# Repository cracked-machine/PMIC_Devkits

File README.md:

# <U>STPMIC1 / PF3000 PMIC Dev Board</U>

#### Overview

Dual development board for evaluating two power management integrated circuits (PMIC) chips:

- STMicroElectronics STPMIC1
- NXP PF3000 Power Management ICs.

These are organised into two independantly powered sub-systems.

Each sub-system has a number of external power/signal connectors, along with a list of the jumpers used to configure how those connectors are routed to/from the PMIC chip. The PMICs are configured directly by modifying registers using either a MCU/MPU via the I2C connectors.

Each output has an LED indicator and testpoint. 
_Note_ that the LED will only light if the PMIC output voltage is set above 2V.

#### Circuit design notes
The schematic has a separate sheet for both sub-systems. There is one for each chip: 

- __DEV__ - The development board sub-system including power/config connectors.
- __MAIN__ - The individual PMIC including the required passive components for bypassing and SMPS/regulator operation. Designed to be reuseable blocks that can easily be incorproated into an existing design.

| STPMIC1 DEV | STPMIC1 MAIN |
|:---:|:---:|
||

| PF3000 DEV | PF3000 MAIN  |
|:---:|:---:|
|||

#### PCB layout notes
This is a four layer PCB design. The layer stackup is:

1. Signal
2. Ground
3. Small signal and power
4. Small signal and ground

Note the ground planes in layer 2 and 4 are connected.

The _docs_ directory contains:
- RevA gerber build files.
- [Bill of Materials](STPMIC1_MC32PF3000_Board/STPMIC1_MC32PF3000_Board/docs/bom/FULL_STPMIC1_MC32PF3000_Board.csv)
- CPL pick and place files.
- Related vendor application notes, datasheets and reference designs.

Custom symbols and footprints used in this project can be found in the [KicadLibrary](https://github.com/cracked-machine/KicadLibrary) repository.

## <U>PMIC #1: NXP PF300</U>

#### <U>Board connector definitions</U>

| Connector | Description | Comment |
|:---:|:---:|:---|
|J15|Wall adaptor power input|3.7V - 5.5V<br>DC Barrel 2.1mm|
|J12|Battery power input|3.1V - 4.5V<br>2.54mm Header|
|J20|I2C debug|1: Ground<br>2: SCL<br>3: SDA|
|J23|Digital Interface<br>(see datasheet)|1: Ground<br>2: STANDBY<br>3: RESETBMCU<br>4: SD_VSEL<br>5: INTB<br>6: PWRON|
|J21|PF3000 Power Output|Ground:<br>2,4,6,8,10,12,14,16,18,20,22,24,26<br><br>1: SW1B Buck <br>3: SW1A Buck <br>5: SWBST Boost<br>7: VSNVS LDO<br>9: VCCSD LDO<br>11: V33 LDO<br> 13: SW3 Buck<br>15: VREFDDR LDO<br>17: LDO4<br> 19: LDO3<br>21: SW2 Buck<br>23: LDO2<br> 25: LDO1

#### <U>Board jumper and switch definitions</U>

Warning: function of jumpers can be inverted using the registers. See datasheet for details.

| Jumper/Switch | Description| Setting | Comment |
|:---:|:---:|:---:|:---|
|JP1|Q2 Pullup|ON|Force Q2 gate to VDBG rail. <br>Use if PGOOD LED becomes erratic.|
|JP2|Q3 Pullup|ON|Force Q3 to VDBG rail. <br>Use if FAIL LED becomes erratic.|
|J13|OTP|3-2|Load OTP values from memory into OTP registers|
|J13|OTP|2-1|Disable OTP memory and load OTP values from fuses. "Try before buy" mode.|
|J16|I2C Bus Power (VDDIO)|3-2|Power from VDGB. 3.3V|
|J16|I2C Bus Power (VDDIO)|2-1|Power from Buck 2 output. 1.8V|
|J14|Digital Interface Power (V_PU)|3-2|Power from J16 output|
|J14|Digital Interface Power (V_PU)|2-1|Power from VSNVS output (fixed 3V)|
|J17|Standby|3-2|Enter standby mode|
|J17|Standby|2-1|Exit standby mode|
|J18|VCC_SD output range|3-2|1.8V to 1.85V|
|J18|VCC_SD output range|2-1|2.85V to 3.3V|
|J19|Power enable|2-1|IC power output is enabled|
|SW5|Power enable| - | Momentary SPST.<br>IC power output is enabled.
|J22|VPWR override|3-2|VPWR enable. <br>Set when J15 DC connector is powered|
|J22|VPWR override|2-1|VPWR disable. <br>Set when J12 battery power connector is powered.<br>Warning: Shorts J15 to ground!|

## <U>PMIC #2: STMicroelectronics STPMIC1</U>

#### <U>Board connector definitions</U>

| Connector | Description | Comment |
|:---:|:---:|:---|
|J2|External VIO|0.5V to 4.2V.<br>I/O voltage (for all digital signals except WAKEUP and PONKEY)|
|J3|External SWIN|0.5V - 7V.<br>External power source for VSWIN pin.
|J4|Wall adaptor power input|0.5V - 7V.<br>DC Barrel 2.1mm|
|J1|Battery power input|0.5V - 7V.<br>2.54mm Header|
|J10|I2C debug|1: Ground<br>2: SCL<br>3: SDA|
|J5|Digital Interface<br>(see datasheet)|1: Ground<br>2: PONKEY (IN)<br>3: WAKEUP (IN)<br>4: RST (BOTH)<br>5: PWRCTL (IN)<br>6: INT (OUT)|
|J21|STPMIC1 Power Output|Ground:<br>2,4,6,8,10,12,14,16,18,20,22,24,26<br><br>1: Buck2 <br>3: Buck1 <br>5: LDO4<br>7: VSWOUT LDO<br>9: VOTG LDO<br>11: Boost<br> 13: Buck3<br>15: Buck4<br>17: LDO1<br> 19: LDO6<br>21: LDO5<br>23: LDO2<br> 25: VREFDDR LDO<br>27: LDO3|

#### <U>Board jumper and switch definitions</U>

Warning: function of jumpers can be inverted using the registers. See datasheet for details.

| Jumper/Switch | Description| Setting | Comment |
|:---:|:---:|:---:|:---|
|J6|VIO source select|3-2|Power source from Buck3 output|
|J6|VIO source select|2-1|Power source from VIO Ext (J2)|
|J7|VSWIN source select|3-2|Power source from BOOST output|
|J7|VSWIN source select|2-1|Power source from SWIN Ext (J3)|
|J8|LDO3 source select|1-2|Power source from VBAT (J4 or J1)|
|J8|LDO3 source select|3-4|Power source from BUCK2 output|
|J8|LDO3 source select|5-6|Power source from BUCK2 output|
|J9|PWRCTL Pullup/Pulldown|3-2|Pullup from VIO (J6)|
|J9|PWRCTL Pullup/Pulldown|2-1|Pulldown to ground|
|SW1|Wakeup enable| - |Momentary SPST to VBAT|
|SW2|IC Reset| - |Momentary SPST to ground|
|SW3|PONKEY| - |User power on key|

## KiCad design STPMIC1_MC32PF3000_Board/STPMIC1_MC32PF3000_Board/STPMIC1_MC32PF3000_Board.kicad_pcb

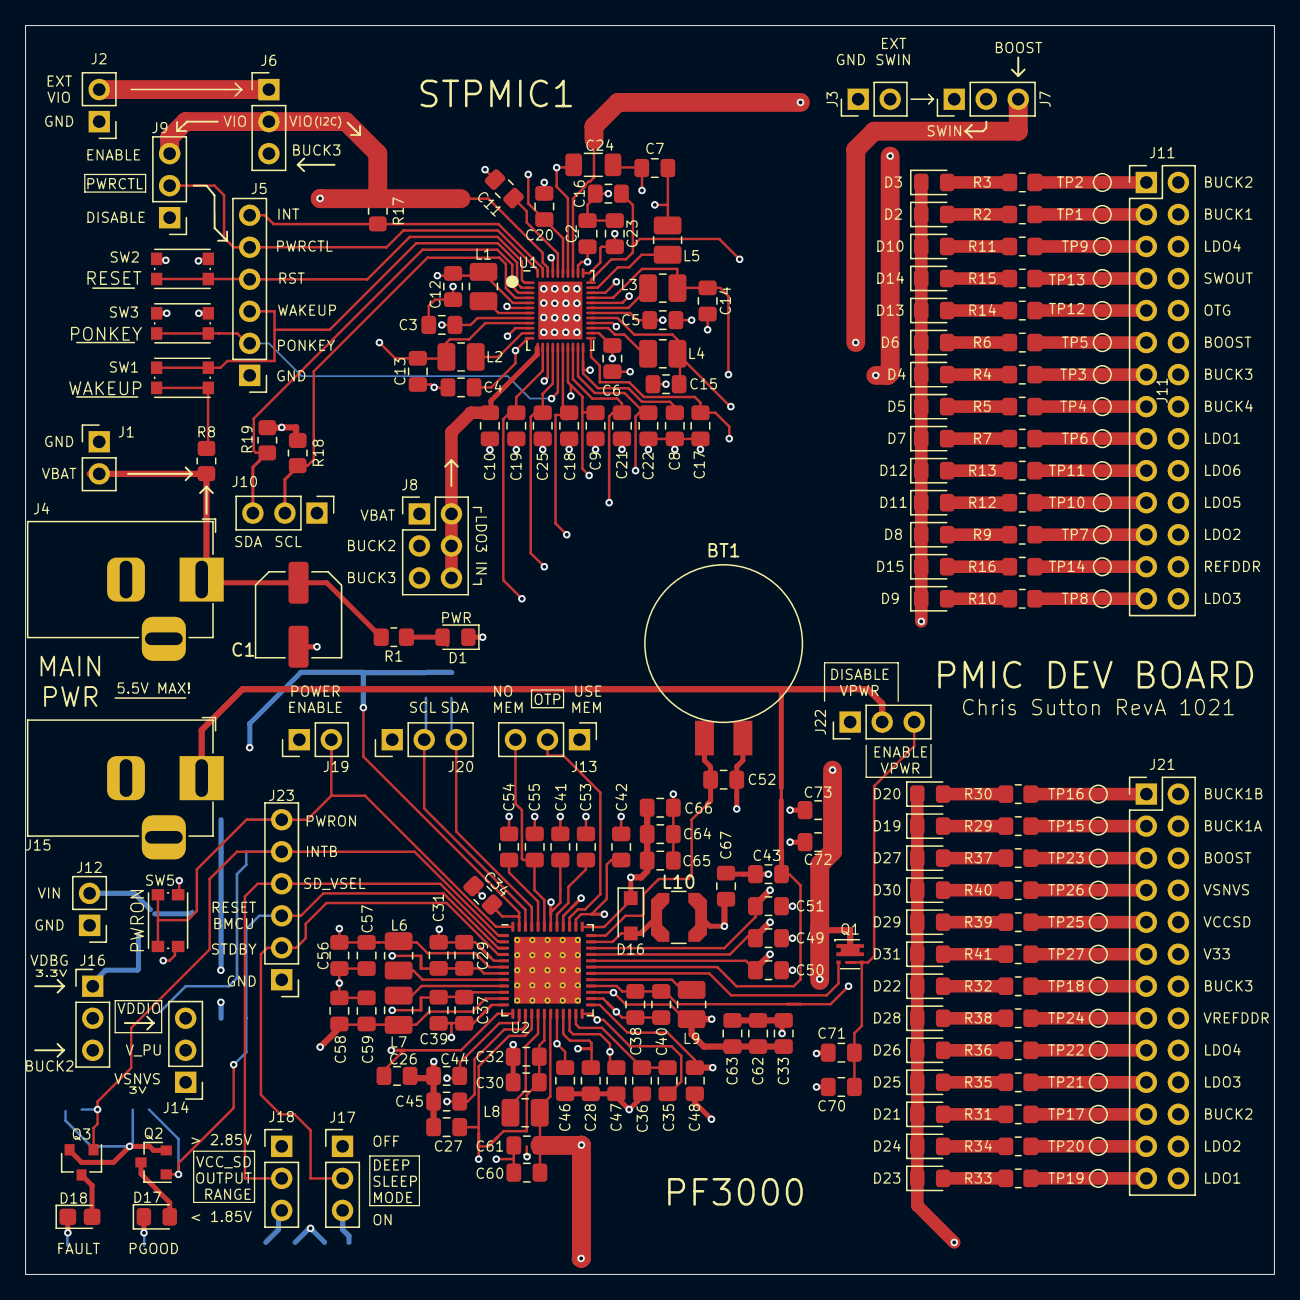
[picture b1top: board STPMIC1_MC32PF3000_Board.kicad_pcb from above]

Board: 4 copper layers, 99.1 x 99.1 mm, 232 parts (0 on the bottom side), 121 nets.

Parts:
BT1: Battery_Cell; ML1220_F1BN
C1: 100uF; C_Elec_6.3x7.7
C2, C11, C17, C18, C20, C21, C22, C23, C43, C45, C47, C50: 4.7uF; C_0805_2012Metric_Pad1.18x1.45mm_HandSolder
C3, C4, C5, C6, C7, C10, C19, C29, C30, C37, C38, C42, C67, C69: 10uF; C_0805_2012Metric_Pad1.18x1.45mm_HandSolder
C8, C9, C25, C26, C27, C28, C33, C41, C48, C53, C55, C68: 1uF; C_0805_2012Metric_Pad1.18x1.45mm_HandSolder
C12, C13, C14, C15, C16, C44, C46, C49, C56, C57, C58, C59, C60, C61, C62, C63, C64, C65, C72, C73: 22uF; C_0805_2012Metric_Pad1.18x1.45mm_HandSolder
C24: 220uF; C_1206_3216Metric_Pad1.33x1.80mm_HandSolder
C31, C32, C34, C35, C36, C39, C40: 100nF; C_0805_2012Metric_Pad1.18x1.45mm_HandSolder
C51: 470nF; C_0805_2012Metric_Pad1.18x1.45mm_HandSolder
C52, C54: 220nF; C_0805_2012Metric_Pad1.18x1.45mm_HandSolder
C66: 10nF; C_0805_2012Metric_Pad1.18x1.45mm_HandSolder
C70, C71: 47uF; C_0805_2012Metric_Pad1.18x1.45mm_HandSolder
D1, D2, D3, D4, D5, D6, D7, D8, D9, D10, D11, D12, D13, D14, D15, D19, D20, D21, D22, D23, D24, D25, D26, D27, D28, D29, D30, D31: D; LED_0805_2012Metric_Pad1.15x1.40mm_HandSolder
D16: MBR120LSFT3G; D_SOD-123F
D17: PGOOD; LED_0805_2012Metric_Pad1.15x1.40mm_HandSolder
D18: FAULT; LED_0805_2012Metric_Castellated
J1, J2, J3, J12, J19: Conn_01x02; PinHeader_1x02_P2.54mm_Vertical
J4: Barrel_Jack; BarrelJack_Horizontal
J5, J23: Conn_01x06; PinHeader_1x06_P2.54mm_Vertical
J6, J7, J9, J10, J13, J14, J16, J17, J18, J20, J22: Conn_01x03; PinHeader_1x03_P2.54mm_Vertical
J8: Conn_02x03_Odd_Even; PinHeader_2x03_P2.54mm_Vertical
J11: Conn_02x14_Odd_Even; PinHeader_2x14_P2.54mm_Vertical
J15: Barrel_Jack_Switch; BarrelJack_Horizontal
J21: Conn_02x13_Odd_Even; PinHeader_2x13_P2.54mm_Vertical
JP1, JP2: Jumper_NO_Small; SolderJumper-2_P1.3mm_Open_RoundedPad1.0x1.5mm
L1, L2, L3, L4, L5: 1uH; L_1008_2520Metric_Pad1.43x2.20mm_HandSolder
L6, L7, L8, L9: 1.5uH; L_1008_2520Metric_Pad1.43x2.20mm_HandSolder
L10: 2.2uH; L_Coilcraft_LPS4018
NT1, NT2, NT3, NT4, NT5, NT6, NT7, NT8, NT9, NT10, NT11, NT12, NT13, NT14: Net-Tie_2; NetTie-2_SMD_Pad0.254mm
Q1: FDMA908PZ; Vishay_PowerPAK_SC70-6L_Single
Q2, Q3: Q_PMOS_GSD; SOT-23
R1, R2, R3, R4, R5, R6, R7, R8, R9, R10, R11, R12, R13, R14, R15, R16, R18, R19, R27, R28, R29, R30, R31, R32, R33, R34, R35, R36, R37, R38, R39, R40, R41: 2K2; R_0805_2012Metric_Pad1.20x1.40mm_HandSolder
R17: 10K; R_0805_2012Metric_Pad1.20x1.40mm_HandSolder
R20, R21: 4K7; R_0805_2012Metric_Pad1.20x1.40mm_HandSolder
R22, R23, R24, R25, R26: 100K; R_0805_2012Metric_Pad1.20x1.40mm_HandSolder
SW1, SW2, SW3, SW5: SW_SPST; SW_Push_1P1T_NO_CK_KMR2
TP1, TP2, TP3, TP4, TP5, TP6, TP7, TP8, TP9, TP10, TP11, TP12, TP13, TP14, TP15, TP16, TP17, TP18, TP19, TP20, TP21, TP22, TP23, TP24, TP25, TP26, TP27: TestPoint; TestPoint_Pad_D1.0mm
U1: STPMIC1; WQFN-44L_EP_5x6_Pitch0.4mm
U2: PF3000; QFN-48-1EP_7x7mm_P0.5mm_EP5.3x5.3mm_ThermalVias
U3: SE8233X2; SOT-23

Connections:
/PF3000_Board/INTB: J23.5, JP2.1, Q3.1, R25.2, U2.1
/PF3000_Board/LDO1_OUT: C44.2, J21.25, R33.1, TP19.1, U2.14
/PF3000_Board/LDO2_OUT: C45.2, J21.23, R34.1, TP20.1, U2.15
/PF3000_Board/LDO3_OUT: C46.2, J21.19, R35.1, TP21.1, U2.20
/PF3000_Board/LDO4_OUT: C47.2, J21.17, R36.1, TP22.1, U2.22
/PF3000_Board/PF3000/LDOG: Q1.3, U2.30
/PF3000_Board/PF3000/LICELL_TO_BAT: BT1.1, C52.2, U2.36
/PF3000_Board/PWRON: J19.2, J23.6, R26.2, SW5.2, U2.48
/PF3000_Board/RESETBMCU: J23.3, JP1.1, Q2.1, R23.2, U2.3
/PF3000_Board/SCL: J20.2, R21.2, U2.46
/PF3000_Board/SDA: J20.3, R20.1, U2.45
/PF3000_Board/SD_VSEL: J18.2, J23.4, U2.2
/PF3000_Board/STANDBY: J17.2, J23.2, U2.4
/PF3000_Board/SW1A_OUT: C56.2, C57.2, J21.3, L6.2, R29.1, TP15.1, U2.6
/PF3000_Board/SW1B_OUT: C58.2, C59.2, J21.1, L7.2, R30.1, TP16.1, U2.11
/PF3000_Board/SW2_OUT: C60.2, C61.2, J16.3, J21.21, L8.2, R31.1, TP17.1, U2.19
/PF3000_Board/SW3_OUT: C33.2, C35.2, C62.2, C63.2, J21.13, L9.2, R32.1, TP18.1, U2.24, U2.27
/PF3000_Board/SWBST_OUT: C64.2, C65.2, C66.2, D16.1, J21.5, R37.1, TP23.1, U2.37
/PF3000_Board/V33_OUT: C50.2, J21.11, R41.1, TP27.1, U2.32
/PF3000_Board/VCCSD_OUT: C49.2, J21.9, R39.1, TP25.1, U2.33
/PF3000_Board/VCOREDIG: C55.2, J13.3, U2.43
/PF3000_Board/VDBG: C69.1, J16.1, JP1.2, JP2.2, Q2.2, Q3.2, U3.2
/PF3000_Board/VDDIO: C34.2, J14.3, J16.2, R20.2, R21.1, U2.47
/PF3000_Board/VDDOTP: J13.2, U2.39
/PF3000_Board/VIN: C67.1, C68.2, C72.1, C73.2, J12.2, L10.2, NT1.1, NT2.1, NT3.1, NT4.1, NT5.1, NT6.1, NT7.1, NT8.1, NT9.1, Q1.1, U3.3
/PF3000_Board/VPWR: J15.1, J22.2, NT10.1
/PF3000_Board/VREFDDR_OUT: C48.2, J21.15, R38.1, TP24.1, U2.25
/PF3000_Board/VSNVS_OUT: C51.2, J14.1, J21.7, R40.1, TP26.1, U2.34
/PF3000_Board/V_PU: J14.2, R22.1, R23.1, R24.1, R25.1, R26.1
/STPMIC1_Board/INT: J5.6, R17.2, U1.43
/STPMIC1_Board/PONKEY: J5.2, SW3.2, U1.17
/STPMIC1_Board/PWRCTL: J5.5, J9.2, U1.44
/STPMIC1_Board/RST: J5.4, SW2.2, U1.1
/STPMIC1_Board/SCL: J10.2, R18.2, U1.4
/STPMIC1_Board/SDA: J10.3, R19.2, U1.3
/STPMIC1_Board/SWIN_Ext: J3.2, J7.1
/STPMIC1_Board/VBAT: C1.1, C2.1, C3.1, C4.1, C5.1, C6.1, C7.1, C8.1, C9.1, J1.2, J4.1, J8.1, L5.1, R1.1, R8.1, U1.8, U1.12, U1.19, U1.22, U1.24, U1.28, U1.36
/STPMIC1_Board/VBOOST: C16.1, J7.3, J11.11, R6.1, TP5.1, U1.34
/STPMIC1_Board/VBUCK1: C12.1, J11.3, L1.2, R2.1, TP1.1, U1.5
/STPMIC1_Board/VBUCK2: C13.1, J8.3, J11.1, L2.2, R3.1, TP2.1, U1.9
/STPMIC1_Board/VBUCK3: C14.1, J6.3, J8.5, J11.13, L3.2, R4.1, TP3.1, U1.31
/STPMIC1_Board/VBUCK4: C15.1, J11.15, L4.2, R5.1, TP4.1, U1.27
/STPMIC1_Board/VIO: J6.2, J9.3, R17.1, R18.1, R19.1, U1.42
/STPMIC1_Board/VIO_Ext: J2.2, J6.1
/STPMIC1_Board/VLDO1: C17.1, J11.17, R7.1, TP6.1, U1.23
/STPMIC1_Board/VLDO2: C18.1, J11.23, R9.1, TP7.1, U1.18
/STPMIC1_Board/VLDO3: C19.1, J11.27, R10.1, TP8.1, U1.14
/STPMIC1_Board/VLDO4: C20.1, J11.5, R11.1, TP9.1, U1.39
/STPMIC1_Board/VLDO5: C21.1, J11.21, R12.1, TP10.1, U1.20
/STPMIC1_Board/VLDO6: C22.1, J11.19, R13.1, TP11.1, U1.21
/STPMIC1_Board/VOTG: C23.1, J11.9, R14.1, TP12.1, U1.35
/STPMIC1_Board/VREFDDR: C25.1, J11.25, R16.1, TP14.1, U1.16
/STPMIC1_Board/VSWOUT: C24.1, J11.7, R15.1, TP13.1, U1.38
/STPMIC1_Board/WAKEUP: J5.3, SW1.1, U1.2
/STPMIC1_Board/sheet60878B3D/LDO3_IN: C10.1, J8.2, J8.4, J8.6, U1.13
/STPMIC1_Board/sheet60878B3D/VSWIN: J7.2, U1.37
GNDS: BT1.2, C1.2, C2.2, C3.2, C4.2, C5.2, C6.2, C7.2, C8.2, C9.2, C10.2, C11.2, C12.2, C13.2, C14.2, C15.2, C16.2, C17.2, C18.2, C19.2, C20.2, C21.2, C22.2, C23.2, C24.2, C25.2, C26.1, C27.1, C28.1, C29.1, C30.1, C31.1, C32.1, C33.1, C34.1, C36.1, C37.1, C38.1, C39.1, C40.1, C41.1, C42.1, C43.1, C44.1, C45.1, C46.1, C47.1, C48.1, C49.1, C50.1, C51.1, C52.1, C53.1, C54.1, C55.1, C56.1, C57.1, C58.1, C59.1, C60.1, C61.1, C62.1, C63.1, C64.1, C65.1, C66.1, C67.2, C68.1, C69.2, C70.1, C71.2, C72.2, C73.1, D1.1, D2.1, D3.1, D4.1, D5.1, D6.1, D7.1, D8.1, D9.1, D10.1, D11.1, D12.1, D13.1, D14.1, D15.1, D19.1, D20.1, D21.1, D22.1, D23.1, D24.1, D25.1, D26.1, D27.1, D28.1, D29.1, D30.1, D31.1, J1.1, J2.1, J3.1, J4.2, J5.1, J9.1, J10.1, J11.2, J11.4, J11.6, J11.8, J11.10, J11.12, J11.14, J11.16, J11.18, J11.20, J11.22, J11.24, J11.26, J11.28, J12.1, J13.1, J15.2, J17.1, J18.1, J19.1, J20.1, J21.2, J21.4, J21.6, J21.8, J21.10, J21.12, J21.14, J21.16, J21.18, J21.20, J21.22, J21.24, J21.26, J22.1, J23.1, NT11.2, NT12.2, NT13.2, NT14.2, R27.1, R28.1, SW2.1, SW3.1, SW5.1, U1.6, U1.10, U1.15, U1.26, U1.30, U1.32, U1.41, U3.1
unnamed: C11.1, U1.40
unnamed: C26.2, NT1.2, U2.13
unnamed: C27.2, NT2.2, U2.16
unnamed: C28.2, NT3.2, U2.21
unnamed: C29.2, C31.2, NT4.2, U2.7
unnamed: C30.2, C32.2, NT5.2, U2.18
unnamed: C35.1, C36.2, U2.23
unnamed: C37.2, C39.2, NT6.2, U2.10
unnamed: C38.2, C40.2, NT7.2, U2.28
unnamed: C41.2, NT9.2, U2.42
unnamed: C42.2, NT8.2, U2.38
unnamed: C43.2, NT10.2, U2.31
unnamed: C53.2, U2.41
unnamed: C54.2, U2.44
unnamed: C70.2, C71.1, J22.3, Q1.4
unnamed: D1.2, R1.2
unnamed: D2.2, R2.2
unnamed: D3.2, R3.2
unnamed: D4.2, R4.2
unnamed: D5.2, R5.2
unnamed: D6.2, R6.2
unnamed: D7.2, R7.2
unnamed: D8.2, R9.2
unnamed: D9.2, R10.2
unnamed: D10.2, R11.2
unnamed: D11.2, R12.2
unnamed: D12.2, R13.2
unnamed: D13.2, R14.2
unnamed: D14.2, R15.2
unnamed: D15.2, R16.2
unnamed: D16.2, L10.1, U2.35
unnamed: D17.1, R27.2
unnamed: D17.2, Q2.3
unnamed: D18.1, R28.2
unnamed: D18.2, Q3.3
unnamed: D19.2, R29.2
unnamed: D20.2, R30.2
unnamed: D21.2, R31.2
unnamed: D22.2, R32.2
unnamed: D23.2, R33.2
unnamed: D24.2, R34.2
unnamed: D25.2, R35.2
unnamed: D26.2, R36.2
unnamed: D27.2, R37.2
unnamed: D28.2, R38.2
unnamed: D29.2, R39.2
unnamed: D30.2, R40.2
unnamed: D31.2, R41.2
unnamed: J17.3, R22.2
unnamed: J18.3, R24.2
unnamed: L1.1, U1.7
unnamed: L2.1, U1.11
unnamed: L3.1, U1.29
unnamed: L4.1, U1.25
unnamed: L5.2, U1.33
unnamed: L6.1, U2.8
unnamed: L7.1, U2.9
unnamed: L8.1, U2.17
unnamed: L9.1, U2.29
unnamed: NT11.1, U2.12
unnamed: NT12.1, U2.26
unnamed: NT13.1, U2.40
unnamed: NT14.1, U2.5
unnamed: R8.2, SW1.2

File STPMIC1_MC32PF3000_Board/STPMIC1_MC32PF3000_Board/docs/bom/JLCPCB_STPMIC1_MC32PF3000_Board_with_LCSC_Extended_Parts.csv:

Comment,Designator,Footprint,LCSC
"Battery_Cell","BT1","Panasonic_ML_series:ML1220_F1BN","~"
"100uF","C1","Capacitor_SMD:C_Elec_6.3x7.7","C127971"
"22uF","C12,C13,C14,C15,C16,C44,C46,C49,C56,C57,C58,C59,C60,C61,C62,C63,C64,C65,C72,C73","Capacitor_SMD:C_0805_2012Metric_Pad1.18x1.45mm_HandSolder","C45783"
"4.7uF","C2,C11,C17,C18,C20,C21,C22,C23,C43,C45,C47,C50","Capacitor_SMD:C_0805_2012Metric_Pad1.18x1.45mm_HandSolder","C1779"
"10uF","C3,C4,C5,C6,C7,C10,C19,C29,C30,C37,C38,C42,C67,C69","Capacitor_SMD:C_0805_2012Metric_Pad1.18x1.45mm_HandSolder","C15850"
"220uF","C24","Capacitor_SMD:C_1206_3216Metric_Pad1.33x1.80mm_HandSolder","~"
"1uF","C8,C9,C25,C26,C27,C28,C33,C41,C48,C53,C55,C68","Capacitor_SMD:C_0805_2012Metric_Pad1.18x1.45mm_HandSolder","C28323"
"100nF","C31,C32,C34,C35,C36,C39,C40","Capacitor_SMD:C_0805_2012Metric_Pad1.18x1.45mm_HandSolder","C49678"
"470nF","C51","Capacitor_SMD:C_0805_2012Metric_Pad1.18x1.45mm_HandSolder","C13967"
"220nF","C52,C54","Capacitor_SMD:C_0805_2012Metric_Pad1.18x1.45mm_HandSolder","C5378"
"10nF","C66","Capacitor_SMD:C_0805_2012Metric_Pad1.18x1.45mm_HandSolder","C1710"
"47uF","C70,C71","Capacitor_SMD:C_0805_2012Metric_Pad1.18x1.45mm_HandSolder","C16780"
"D","D1,D2,D3,D4,D5,D6,D7,D8,D9,D10,D11,D12,D13,D14,D15,D19,D20,D21,D22,D23,D24,D25,D26,D27,D28,D29,D30,D31","LED_SMD:LED_0805_2012Metric_Pad1.15x1.40mm_HandSolder","C84256"
"MBR120LSFT3G","D16","Diode_SMD:D_SOD-123F","C190475"
"PGOOD","D17","LED_SMD:LED_0805_2012Metric_Pad1.15x1.40mm_HandSolder"," C84256"
"FAULT","D18","LED_SMD:LED_0805_2012Metric_Castellated"," C84256"
"Conn_01x03","J6,J7,J9,J10,J13,J14,J16,J17,J18,J20,J22","Connector_PinHeader_2.54mm:PinHeader_1x03_P2.54mm_Vertical","~"
"Conn_02x14_Odd_Even","J11","Connector_PinHeader_2.54mm:PinHeader_2x14_P2.54mm_Vertical","~"
"Barrel_Jack_Switch","J15","Connector_BarrelJack:BarrelJack_Horizontal","~"
"Conn_02x13_Odd_Even","J21","Connector_PinHeader_2.54mm:PinHeader_2x13_P2.54mm_Vertical","~"
"Conn_01x02","J1,J2,J3,J12,J19","Connector_PinHeader_2.54mm:PinHeader_1x02_P2.54mm_Vertical","~~~~~~~~~~"
"Barrel_Jack","J4","Connector_BarrelJack:BarrelJack_Horizontal","~"
"Conn_01x06","J5,J23","Connector_PinHeader_2.54mm:PinHeader_1x06_P2.54mm_Vertical","~"
"Conn_02x03_Odd_Even","J8","Connector_PinHeader_2.54mm:PinHeader_2x03_P2.54mm_Vertical","~"
"Jumper_NO_Small","JP1,JP2","Jumper:SolderJumper-2_P1.3mm_Open_RoundedPad1.0x1.5mm","~"
"1uH","L1,L2,L3,L4,L5","Inductor_SMD:L_1008_2520Metric_Pad1.43x2.20mm_HandSolder","~"
"2.2uH","L10","Inductor_SMD:L_Coilcraft_LPS4018","~"
"1.5uH","L6,L7,L8,L9","Inductor_SMD:L_1008_2520Metric_Pad1.43x2.20mm_HandSolder","~"
"Net-Tie_2","NT1,NT2,NT3,NT4,NT5,NT6,NT7,NT8,NT9,NT10,NT11,NT12,NT13,NT14","TinyNetTies:NetTie-2_SMD_Pad0.254mm","~"
"FDMA908PZ","Q1","Package_TO_SOT_SMD:Vishay_PowerPAK_SC70-6L_Single","~"
"Q_PMOS_GSD","Q2,Q3","Package_TO_SOT_SMD:SOT-23","~"
"2K2","R1,R2,R3,R4,R5,R6,R7,R8,R9,R10,R11,R12,R13,R14,R15,R16,R18,R19,R27,R28,R29,R30,R31,R32,R33,R34,R35,R36,R37,R38,R39,R40,R41","Resistor_SMD:R_0805_2012Metric_Pad1.20x1.40mm_HandSolder","C17520"
"10K","R17","Resistor_SMD:R_0805_2012Metric_Pad1.20x1.40mm_HandSolder","C17414"
"4K7","R20,R21","Resistor_SMD:R_0805_2012Metric_Pad1.20x1.40mm_HandSolder","C17414"
"100K","R22,R23,R24,R25,R26","Resistor_SMD:R_0805_2012Metric_Pad1.20x1.40mm_HandSolder","C17407"
"SW_SPST","SW1,SW2,SW3,SW5","Button_Switch_SMD:SW_Push_1P1T_NO_CK_KMR2","~"
"TestPoint","TP1,TP2,TP3,TP4,TP5,TP6,TP7,TP8,TP9,TP10,TP11,TP12,TP13,TP14,TP15,TP16,TP17,TP18,TP19,TP20,TP21,TP22,TP23,TP24,TP25,TP26,TP27","TestPoint:TestPoint_Pad_D1.0mm","~"
"STPMIC1","U1","STPMIC1:WQFN-44L_EP_5x6_Pitch0.4mm",""
"PF3000","U2","Package_DFN_QFN:QFN-48-1EP_7x7mm_P0.5mm_EP5.3x5.3mm_ThermalVias",""
"SE8233X2","U3","Package_TO_SOT_SMD:SOT-23","C437587"

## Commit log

2021-03-02 Added STPMIC1 and PF3000 (no layout) designs
2021-03-02 updated schema document
2021-03-06 Completed RevA layout
2021-03-07 updated RevA Layout
2021-03-07 updated docs
2021-03-09 Completed RevA
2021-03-09 updated readme
    Added connector and jumper/switch details
2021-03-09 added full BOM csv
